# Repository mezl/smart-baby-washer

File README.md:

<h1 align="center">Smart Baby Washer</h1>

<p align="center">
  <b>App and Home Assistant control for a baby-bottle washer, from an ESP32-C3
  that plugs inline on the panel cable.</b>
</p>

- Sits on the 4-pin serial link between the front panel and the controller board,
  forwarding every frame and rewriting any byte in flight.
- **Reversible** — `CN2` is a plug-in connector, so the module goes inline on the
  existing cable. Nothing cut, nothing soldered to the OEM board.
- ⚠️ **Verified on two Momcozy D8 units** — an early button-panel one (board
  `BBW04001-UL-P`) and a later touch-panel one. Same firmware, unmodified, on
  both. See [what differs](#what-differs-between-the-two-units)

## What it does

- **Web app + HTTP API** — pick a program, start/stop/resume, watch state,
  temperature and stage.
- **Home Assistant** — sensors, buttons, dashboard, notifications. Plain REST; no
  MQTT, no custom component.
- **Cycle runner** — six stock programs plus six of your own; durations and
  temperature targets persist; fills end on flow count, not a timer.
- **Interlocks the machine lacks** — no heater without a verified fill; pause on
  lid-open or no water; abort on over temperature, fill stall, fault bit or dead link.
- **Diagnostics** — drive each load on its own, inject `E0` `E3` `E4` `E5` `E7`
  (`E1`/`E6` have no bit), or run a whole cycle with nothing energised.
- **Live link decode** both directions, raw and rewritten, with temperature and
  flow graphs.
- Local only, no cloud. Logging is host-side; the ESP32 stores nothing.

> ⚠️ It can drive 120 V heaters and a water pump directly, and the machine's own
> controller will not stop you. Read [`docs/safety.md`](docs/safety.md) first.

## What you build

- XIAO ESP32-C3 + a 4-channel BSS138 level shifter. Perfboard is enough; the
  carrier board in [`hardware/pcb/`](hardware/pcb/) is tidier, not better.
- Ground and +5 V pass straight through, so the panel never loses supply.
- ⚠️ Wire to the shifter's **printed pad names** — with HV facing the machine the
  pads read 4·3·2·1 down the board. The photo inset in the diagram shows it.
- 💡 Fit the external antenna. Inside a metal and wet plastic appliance the
  on-board one struggles, and losing WiFi means losing OTA.

<p align="center">
  
  &nbsp;
  
</p>

## Quick start

```bash
cp firmware/include/secrets.h.example firmware/include/secrets.h   # WiFi + OTA password
cd firmware
pio run -e c3 -t upload
```

- Open `http://baby-washer.local/`.
- **Start in LISTEN mode** — it cannot drive a line, so nothing can hurt the
  machine while you confirm the wiring.

## Docs

1. ⚠️ [**safety.md**](docs/safety.md) — what the machine does *not* protect you from
2. [**build.md**](docs/build.md) — parts, tapping the link, level shifting, wiring
3. [**flash.md**](docs/flash.md) — firmware, OTA, not bricking it out of reach
4. [**use.md**](docs/use.md) — the app, the engineering page, Home Assistant

Reference: [board.md](docs/board.md) · [protocol.md](docs/protocol.md) ·
[water-plumbing diagram](docs/diagrams/water-plumbing.svg) ·
[cycles.md](docs/cycles.md) · [api.md](docs/api.md) ·
[troubleshooting.md](docs/troubleshooting.md) · [hardware/pcb/](hardware/pcb/)

## Does it fit my machine?

Verified on **two** Momcozy D8 units — an early one (board `BBW04001-UL-P`,
button panel) and a later one (touch panel). Same 9600 8N1 link, same frame
layout, same load bitmap, and the same firmware ran both unmodified.

| | |
|---|---|
| Momcozy D8, either revision | works; the differences below are cosmetic to the protocol |
| Another Momcozy, different board | the link will likely decode, but treat every load bit as unknown until you watch it act |
| Any washer with a separate panel | the approach applies; everything past that is your own work |

- Minimum requirement: a separate front panel talking to a controller over a 4-pin
  connector carrying ground, +5 V and two signal lines.
- [`docs/protocol.md`](docs/protocol.md) has the frame format;
  `POST /api/detect` finds the pin map without ever driving a line.
- A capture from a non-D8 machine is useful — open an issue with `/api/frames`
  output and the board part number.

### What differs between the two units

Measured across 4165 frames from the early unit and 1699 from the later one.

| | early (button panel) | later (touch panel) |
|---|---|---|
| controller byte 6 | `0x02` | **`0x03`** — the only byte that differs by revision |
| controller byte 4 | `0x04` | `0x04` |
| status bit 6 | seen only when starved of panel frames | also asserted **spontaneously**, held for hours, with a byte-perfect link |
| lid bits (1 and 7) | reported normally (`0x02`, `0x80`, `0x82`) | **never seen set** in any capture |
| wash pump on `b0` | low-side switch **does not close** — needs the external relay | **works** — no relay needed |
| fill targets | `0x07 / 0x1C / 0x20 / 0x23 / 0xFF` | same five values |
| heater duty | alternates `wash+heat` ↔ `wash-pump-only` | same |

Two of those matter in practice:

⚠️ **`b0` works on the later unit.** The external wash-pump relay in
[build.md](docs/build.md) is a workaround for the early board's dead low-side
switch. Check yours before wiring a relay it does not need — command `b0` during
a wash and listen.

⚠️ **Status bit 6 is the controller's panel-frame-starvation latch.** On the
later unit it latches until mains removal; the panel renders it as `E5`. Any
gap in forwarding — a slow boot, a wedged relay, an interrupted OTA — can
trip it, which is why the firmware bridges the pads in the first milliseconds
of `setup()` and why you should never flash mid-cycle. The full investigation,
including the wrong turns, is in [`docs/postmortem.md`](docs/postmortem.md).

**Do not assume the error-code table transfers.** Ours comes from the early
unit's manual (`BW05`, p.29). A later panel may number its codes differently,
and reading `E5` as "communication failure" on a machine whose link is provably
clean will send you a long way in the wrong direction.

## Licence

MIT — see [`LICENSE`](LICENSE). No affiliation with Momcozy. Names and part
numbers appear for identification only.

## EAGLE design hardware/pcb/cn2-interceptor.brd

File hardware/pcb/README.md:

# CN2 interceptor carrier board

A 18.6 × 27 mm, 2-layer carrier that sits in the CN2 cable between the D8
controller and its front panel. CN2 pins 3 and 4 (GND, +5 V) pass straight
through; pins 1 and 2 are routed through a level shifter to a XIAO ESP32-C3,
which then sees and can rewrite every byte in both directions.

**J2 (panel) on the bottom edge, J1 (controller) on the top**, with the XIAO
between them and U2 nested *inside* the XIAO's 15.24 mm row gap — its own rows
are 10.16 mm apart, so it drops straight into the middle.

Standing the connectors on opposite edges rather than beside the XIAO is what
makes the board narrow: nothing sits left or right of the module except one
routing lane, so the width is the XIAO's row pitch plus that lane and two
edges. It also suits the cable run, since the two CN2 stubs leave the board in
opposite directions, the way they arrive.

### Which connector goes where is not arbitrary

Routing forces `LV1..LV4` onto `D1..D4` in order — they share a 0.94 mm channel
and any other order makes their spans overlap four deep. `D1..D4` are GPIO 3, 4,
5 and 6, and the firmware's as-built map is `rxb=5 txb=6 txp=3 rxp=4`: the
**controller** pair on GPIO5/6 and the **panel** pair on GPIO3/4. GPIO5/6 are
channels 3 and 4, which are the shifter's upper pins — so the controller has to
enter from the top edge.

Swap the connectors and the board still works, but only after swapping the four
`PIN_*` defines. `gen_pcb.py` reads `firmware/include/config.h` on every run and
fails if the two disagree, because a pin map that disagrees with the copper does
not announce itself: frames simply stop decoding.

## ⚠️ Mount U2 on the underside

Packing the shifter inside the XIAO's rows puts the two modules on top of each
other in plan view:

```
XIAO module   17.5 × 21.0 mm   x  0.22 .. 17.72    y  3.00 .. 24.00
shifter       15.7 × 13.2 mm   x  1.12 .. 16.82    y  6.90 .. 20.10
```

The shifter's outline sits entirely inside the XIAO's. On 2.54 mm sockets the
XIAO stands about 8.5 mm off the board and the shifter plus its own headers is
about 12 mm, so **they collide if both are fitted on top.**

**Solder U2 to the reverse side.** The pads are plated through-holes, so it makes
no difference electrically, and the two modules then sit back to back with the
PCB between them. Nothing in the Gerbers changes — it is purely an assembly
choice, but getting it wrong wastes a board.

If you would rather have both parts on top, put the shifter beside the XIAO
instead of between its rows; that costs roughly 14 mm of board length.

## Reading the silkscreen

| Mark | Meaning |
|---|---|
| `PNL` / `CTL` | which cable goes on which edge — panel bottom, controller top |
| `USB` + arrow | the end the XIAO's USB-C port faces |
| `[` `]` bracket | the side the JST latch faces on J1 and J2 |
| square pad | pin 1, on every connector and both modules |

**The USB arrow matters.** `D0` and `5V` are the two pins at the USB end of the
XIAO, and both sit at the low-y end here, so the port faces the **panel**
connector. Fit the module the other way round and every signal lands on the
wrong pin — there is no keying to stop you, and the board looks right.

**The bracket is the JST latch side.** An XH shroud is not symmetric: the ramp
the cable's clip engages is on one long side. Both are marked facing the nearest
board edge, so the clips are reachable from outside once the board is mounted.
Fit one backwards and the clip faces the board and cannot be released.

### ⚠️ USB access is tight — socket the XIAO, and plug USB in first

The USB port faces J2, about 1.4 mm from the connector. On 2.54 mm sockets the
module stands ~8.5 mm off the board, so the port clears the JST *housing* — but
a **mated** panel cable stands about as tall as the USB plug and sits directly
in front of it.

In practice: **plug the USB cable in before the panel cable**, or leave the
panel cable's service loop long enough to swing aside. This is not theoretical
— a whole debugging session on this project ran over USB serial with the radio
disabled, so losing USB access once assembled is a real cost.

If you would rather not live with it, both connectors can go on the **top**
edge, leaving the USB end of the board clear. Two 4-pin connectors need about
19.5 mm side by side, so the board becomes roughly 21 × 24 mm — near enough the
same area, with the USB fully accessible.

## Bill of materials — four parts

| Ref | Part | Notes |
|---|---|---|
| J1 | JST-XH 4-pin, 2.54 mm, vertical | **top** edge — cable to the **controller** CN2 |
| J2 | JST-XH 4-pin, 2.54 mm, vertical | **bottom** edge — cable to the **panel** CN2 |
| U1 | Seeed XIAO ESP32-C3 | 2×7, 2.54 mm pitch, 15.24 mm between rows |
| U2 | 4-channel BSS138 level shifter | 2×6, 2.54 mm pitch |

Plus two 1×7 and two 1×6 header strips if you want the modules socketed rather
than soldered down. Socketing the XIAO is worth it — it keeps `D5`, `D10` and
`D7` reachable for the flow and switch simulation, which is why the board carries
no separate header for them.

## The flow-meter relay is not on this revision

The previous board carried J3/J4, a relay for the flow-meter (FV) cable, so the
ESP32 could pass the real pulses through, rewrite their rate, or synthesise flow
on a dry bench. **It has been removed**, and that removal is most of the size
reduction: six more pins would not share an edge with the CN2 connectors, so
they forced the connectors back onto the left and right sides and the width from
18.6 mm to 31.5 mm — the flow relay cost more board than everything else on it.

If you put it back, the two findings that cost the most to learn are still worth
having:

- **The ESP32-C3 is not 5 V tolerant and there is no channel left to shift the
  flow signal** — all four converter channels are spoken for by CN2.
  `docs/hardware.md` records the meter as having a 10 kΩ internal pull-up and
  warns that running it at 5 V puts 5 V on a non-5V-tolerant GPIO. Measure FV
  Vcc first; if it is 5 V, `GPIO10` needs a divider, or feed the meter from the
  board's 3V3 so the whole signal drops to 3.3 V.
- **Cutting the line removes the meter's pull-up from the controller's input**,
  because that pull-up lives inside the meter and ends up on the far side of the
  break. The simulated output then has to drive the line actively, or the
  controller-side pin needs its own pull-up.

Only `GPIO7` (D5), `GPIO10` (D10) and `GPIO20` (D7) are free and safe on this
part — `GPIO2`, `GPIO8` and `GPIO9` are strapping pins and `GPIO21` emits ROM
boot chatter at every reset. All three stay reachable on the XIAO's own header
if you socket the module, which is the main reason to socket it.

## Connections

| ch | CN2 | | Converter | XIAO | UART |
|---|---|---|---|---|---|
| 1 | J2 PANEL pin 1 — RX, **input** | ← | `HV1` · `LV1` | `D1 / GPIO3` | `Serial1` **TX** |
| 2 | J2 PANEL pin 2 — TX, output | → | `HV2` · `LV2` | `D2 / GPIO4` | `Serial1` **RX** |
| 3 | J1 CONTROLLER pin 1 — TX, output | → | `HV3` · `LV3` | `D3 / GPIO5` | `Serial0` **RX** |
| 4 | J1 CONTROLLER pin 2 — RX, **input** | ← | `HV4` · `LV4` | `D4 / GPIO6` | `Serial0` **TX** |

That is `PIN_RX_BOARD 5`, `PIN_TX_BOARD 6`, `PIN_TX_PANEL 3`, `PIN_RX_PANEL 4` —
the as-built map already in `firmware/include/config.h`, so **a board built from
this needs no firmware change.** `gen_pcb.py` asserts it on every run.

Note this differs from the channel order in
[`docs/wiring.md`](../../docs/wiring.md#as-built--the-authoritative-table), which
describes the hand-wired module: there the controller landed on channels 1 and 2.
The electrical result is identical; only which pair uses which converter channel
moved, so that the connectors could sit on opposite edges.

**The rule that decides every connection is unchanged:** an *output* stub must
land on an ESP32 **RX** pin, an *input* stub must be **driven** by an ESP32 **TX**
pin. Wiring a TX pin to another output is the one way to damage a board.

Power: controller pin 4 = panel pin 4 = converter `HV` = XIAO `5V`, one net.
XIAO `3V3` → converter `LV`. All grounds common.

## ⚠️ Measure the level shifter before ordering

**Row spacing on 4-channel BSS138 modules is not standardised.** SparkFun's
BOB-12009 and most clones use 0.4″ (10.16 mm), but 0.5″ (12.7 mm) modules exist
and look identical in photos. Put calipers across yours, centre of one row to
centre of the other, then set `LS_ROW` at the top of `gen_pcb.py` and regenerate.

This is the single most likely way to get an unusable board back from the fab.

## How small it can go

18.6 × 27 mm is 502 mm², **39 % smaller than the 819 mm² it replaced** and
**41 % narrower** — which is the dimension that decides whether it fits a slot.

The width is now fully accounted for, and there is nothing left in it:

```
  0.5  edge
 16.8  XIAO pad block  (15.24 row pitch + 1.6 pad)
  0.4  clearance
  0.4  the one outer lane, shared by +5V (top) and GND (bottom)
  0.5  edge
 ─────
 18.6
```

The four CN2 signals never need a side lane at all: each connector pin sits
directly under the middle corridor, so it climbs straight out of its own pad
into its shifter pin, turning once. Only +5V and GND have to reach both the
XIAO's right-hand column and both connectors, and they share the single outer
lane one per layer. Remove that lane and the board is 17.8 mm, but those two
nets have nowhere to go.

**The height is set by the XIAO's body, not by its copper.** The pads span
15.24 mm; the module is 21.0 mm long, so it overhangs 2.88 mm at each end,
straight over the connectors. At 24 mm the modules physically sit on both JST
housings — the Gerbers look perfect and the boards arrive unbuildable.
`gen_pcb.py` now checks the module outlines against every connector pad on each
run for exactly this reason.

Going further would need **right-angle connectors** (the overhang stops
mattering and the board returns to ~24 mm), **discrete BSS138s instead of the
module**, which removes 12 through-holes and the nesting problem entirely, or
**4 layers**. Note that none of this saves money: JLCPCB charges the same for
anything up to 100 × 100 mm, so size only buys fit.

## Panelised for a JLCPCB minimum order

JLCPCB's minimum order is **5 pieces**, and its base tier covers any single
design up to **100 × 100 mm** — so a panel of copies costs what one small board
costs. `gen_panel.py` tiles the board into the largest grid that still fits:

```
  5 × 3 = 15 boards      panel 93.0 × 81.0 mm      5 panels = 75 boards
```

```bash
python3 gen_panel.py        # 5 x 3, the largest that fits
python3 gen_panel.py 3 2    # or any smaller grid
```

Output lands in `gerbers-panel/`, with `preview-panel.svg` to eyeball first.
The generator re-runs the board's DRC, connectivity, mechanical and pin-map
checks and refuses to panelise if any fail — a panel of a broken board is 15
broken boards.

### V-scoring, not mouse bites

The boards **abut with no gap**, which is what lets 15 fit. V-scoring needs a
straight line running the full width or height of the panel, and a grid of
identical rectangles is exactly that. Tab-routing would need a ~2 mm slot
between every pair and would cost a column.

Nothing had to change to make the copper safe for it: the board already keeps
every pad and track **0.5 mm** from its edge, and V-scoring wants 0.4 mm.

**The score lines are on their own layer** (`-V_Cut.gbr`), deliberately not on
`Edge_Cuts`. Anything on the outline layer is read as a route, and a router
following those lines would cut the panel into 15 loose boards at the fab
instead of scoring it. `Edge_Cuts` carries the panel border and nothing else.

### Ordering

Upload `gerbers-panel/` as a zip, then on the order page:

| Field | Value |
|---|---|
| Different Design | **1** |
| Delivery Format | **Panel by Customer** |
| Column × Row | **5 × 3** |
| Board size | 93 × 81 mm (JLC fills this from the Gerbers) |

Add a note asking for **V-scoring on the lines in `cn2-interceptor-panel-V_Cut.gbr`**.
Check their rendered preview before paying — it shows the score lines, and that
is the one place a misread would be visible before it is fabricated.

Panelised orders sometimes carry a small surcharge and the rules do change, so
confirm the price at upload rather than trusting this table. If it has moved,
`python3 gen_panel.py 2 2` gives four boards on a 37 × 54 mm panel, and a plain
single board is always `gerbers-kicad/`.

## Files

| | |
|---|---|
| `gen_pcb.py` | the board as explicit geometry — placement, nets, routing, its own DRC, preview |
| `gen_panel.py` | tiles the board into a JLCPCB-sized panel with V-score lines |
| `gen_kicad.py` | builds a native `.kicad_pcb` via the pcbnew API **and runs KiCad's own DRC** |
| `gen_eagle.py` | emits `.sch` and `.brd` from the same model |
| `gen_kicad_sch.py` | emits a native `.kicad_sch` from the same model |
| `cn2-interceptor.kicad_pcb` | native KiCad 7 board — open it, DRC it, edit it |
| `cn2-interceptor.kicad_sch` | native KiCad 7 schematic — nets joined by labels |
| `cn2-interceptor.sch` / `.brd` | Eagle 9 XML, for Eagle / Fusion 360 |
| `gerbers-kicad/` | **exported by KiCad itself** — this is the set to send to a fab |
| `gerbers/` | my own writer's output, kept as a cross-check |
| `gerbers-panel/` | **the 5 × 3 panel** — upload this zip for a 15-up order |
| `drc-report.txt` | KiCad's DRC output from the last run |

Regenerate everything:

```bash
python3 gen_pcb.py      # geometry DRC + connectivity + my gerbers + preview.svg
python3 gen_kicad.py    # .kicad_pcb + KiCad's own DRC report
python3 gen_kicad_sch.py  # .kicad_sch
python3 gen_eagle.py    # .sch + .brd   (refuses to run if the DRC fails)

kicad-cli pcb export gerbers --output gerbers-kicad \
  --layers F.Cu,B.Cu,F.Mask,B.Mask,F.SilkS,Edge.Cuts \
  --no-x2 --subtract-soldermask cn2-interceptor.kicad_pcb
```

There is one source of truth. The schematic, the board and the Gerbers are three
renderings of the same Python model, so they cannot drift apart.

## What has been checked, and what has not

**Checked by KiCad itself** (`gen_kicad.py`, via `pcbnew.WriteDRCReport`):

```
violations       0   (excluding 4 lib_footprint_issues, see below)
unconnected pads 0
footprint errors 0
```

The four remaining reports are all `lib_footprint_issues: the current
configuration does not include the library 'cn2interceptor'` — the footprints are
generated into the board file rather than pulled from an installed library, so
KiCad cannot find a library to check them against. That is a bookkeeping
complaint, not a geometry or connectivity one.

**Checked by `gen_pcb.py`** on every run, independently of KiCad:

- 2186 pairwise clearance checks at 0.20 mm — copper-to-copper on each layer,
  and every track against every through-hole pad on both layers
- annular ring ≥ 0.30 mm, drill ≥ 0.30 mm, 0.5 mm edge keepout
- connectivity: every pad is on a net, every net has ≥ 2 pads, and every net
  forms a single connected island rather than two stranded halves
- both Eagle files parse as well-formed XML
- the board's pin map is compared against `firmware/include/config.h` and the
  run fails on a mismatch
- module bodies (not just their pads) are checked against every connector pad
- silkscreen is checked to stay on the board and off every pad

**Not checked.** Be clear-eyed about this list:

- **Nothing has been fabricated.** No board has been made or assembled.
- **The Eagle `.sch`/`.brd` have not been opened in Eagle or Fusion.** They parse
  as well-formed XML and are generated from the same verified model, but no Eagle
  install has confirmed they import cleanly. The KiCad board has been through
  KiCad's own DRC and Gerber export.
- **No ERC has been run.** KiCad 7's CLI has no `sch erc` command (that arrived
  in KiCad 8). The `.kicad_sch` parses and plots cleanly through `kicad-cli sch
  export`, which is not the same as passing ERC — open it in Eeschema and run
  ERC if you want that confirmed.
- **Footprint dimensions come from datasheets, not from measuring your parts.**
  The XIAO's 15.24 mm row spacing is well documented; the level shifter's is not
  — see the warning above.
- **No thermal or current analysis.** It carries logic signals and the panel's
  own 5 V supply, which the OEM cable already carried, so this is unlikely to
  matter. It has not been calculated.

**Before ordering:** open the Gerbers in a viewer (JLCPCB and PCBWay both show
you the rendered board at upload), check the level shifter footprint against your
actual module, and confirm the JST-XH pin order matches your cable.

## Safety

The board carries the panel's 5 V supply and its data lines. It does not touch
mains. But what you can then *do* with it does —
see [`docs/safety.md`](../../docs/safety.md): byte 1 of the panel frame is a
direct load bitmap, and three of its bits fire heaters with no cycle running and
no water in the machine.

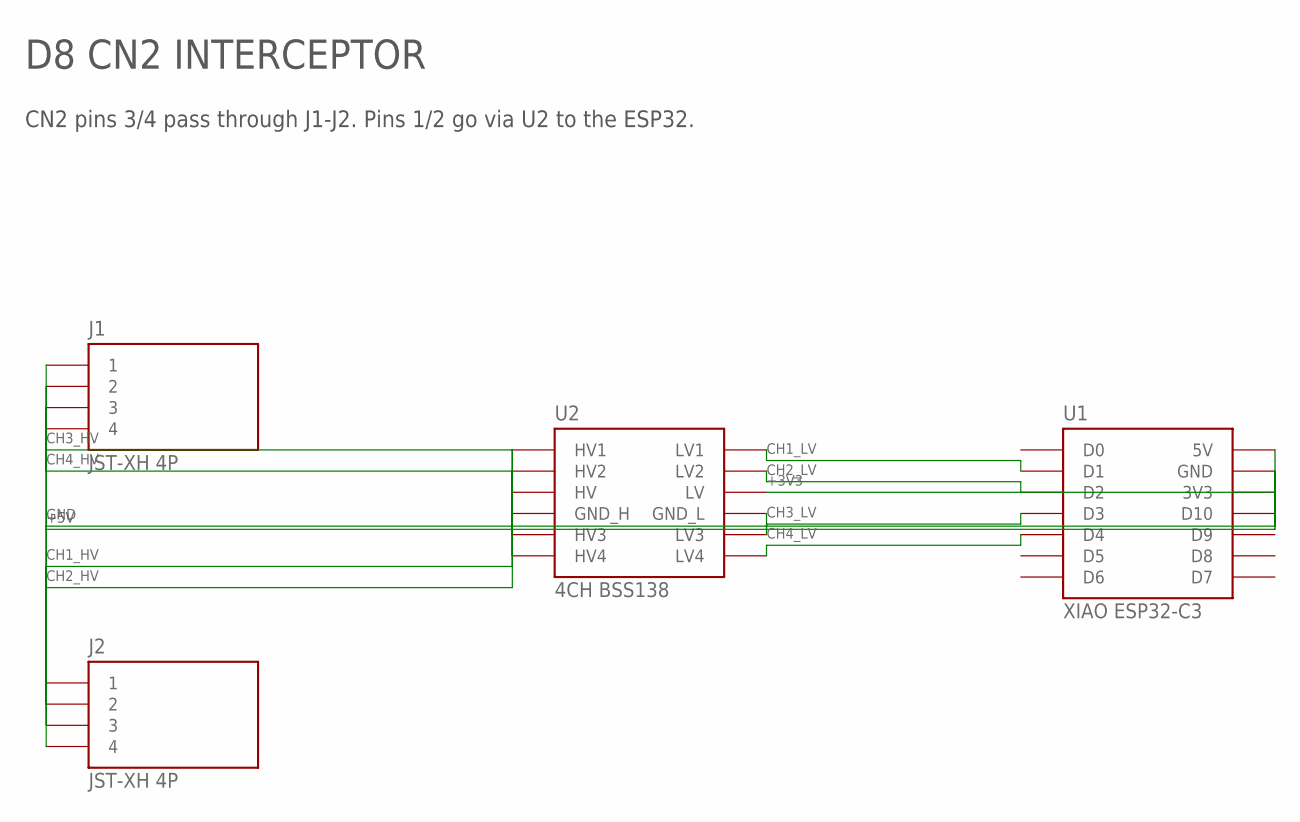
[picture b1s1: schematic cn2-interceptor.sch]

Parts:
J1, J2: JST-XH 4P; JST_XH_4
U1: XIAO ESP32-C3; XIAO_2X7
U2: 4CH BSS138; LS_2X6

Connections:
+3V3: U1.3V3, U2.LV
+5V: J1.4, J2.4, U1.5V, U2.HV
CH1_HV: J2.1, U2.HV1
CH1_LV: U1.D1, U2.LV1
CH2_HV: J2.2, U2.HV2
CH2_LV: U1.D2, U2.LV2
CH3_HV: J1.1, U2.HV3
CH3_LV: U1.D3, U2.LV3
CH4_HV: J1.2, U2.HV4
CH4_LV: U1.D4, U2.LV4
GND: J1.3, J2.3, U1.GND, U2.GND_H, U2.GND_L

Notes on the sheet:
D8 CN2 INTERCEPTOR
CN2 pins 3/4 pass through J1-J2. Pins 1/2 go via U2 to the ESP32.

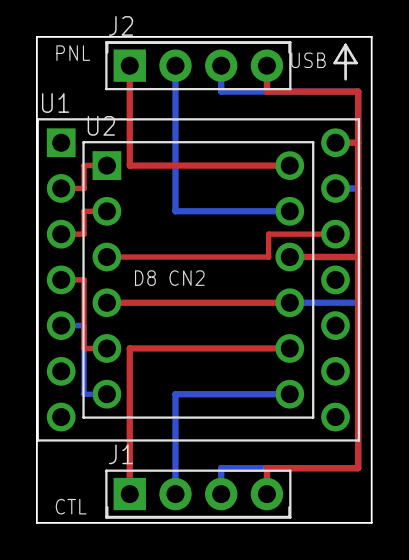
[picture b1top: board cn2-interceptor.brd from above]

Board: 2 copper layers, 18.6 x 27.0 mm, 4 parts (0 on the bottom side), 11 nets.

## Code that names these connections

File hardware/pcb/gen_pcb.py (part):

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
# ch1/ch2 = PANEL pair on D1/D2 (GPIO3/4);  ch3/ch4 = CONTROLLER pair on
# D3/D4 (GPIO5/6). Matches firmware config.h exactly: rxb=5 txb=6 txp=3 rxp=4.
net("CH1_HV", J2[0], LS["HV1"]);  net("CH1_LV", LS["LV1"], X["D1"])  # panel RX  <- GPIO3
net("CH2_HV", J2[1], LS["HV2"]);  net("CH2_LV", LS["LV2"], X["D2"])  # panel TX  -> GPIO4
net("CH3_HV", J1[0], LS["HV3"]);  net("CH3_LV", LS["LV3"], X["D3"])  # ctrl  TX  -> GPIO5
net("CH4_HV", J1[1], LS["HV4"]);  net("CH4_LV", LS["LV4"], X["D4"])  # ctrl  RX  <- GPIO6

NC = [X["D0"], X["D5"], X["D6"], X["D10"], X["D9"], X["D8"], X["D7"]]
for p in NC: p.net = "NC"
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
